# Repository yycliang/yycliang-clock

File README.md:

# yycliang-clock
 My first HPS clock

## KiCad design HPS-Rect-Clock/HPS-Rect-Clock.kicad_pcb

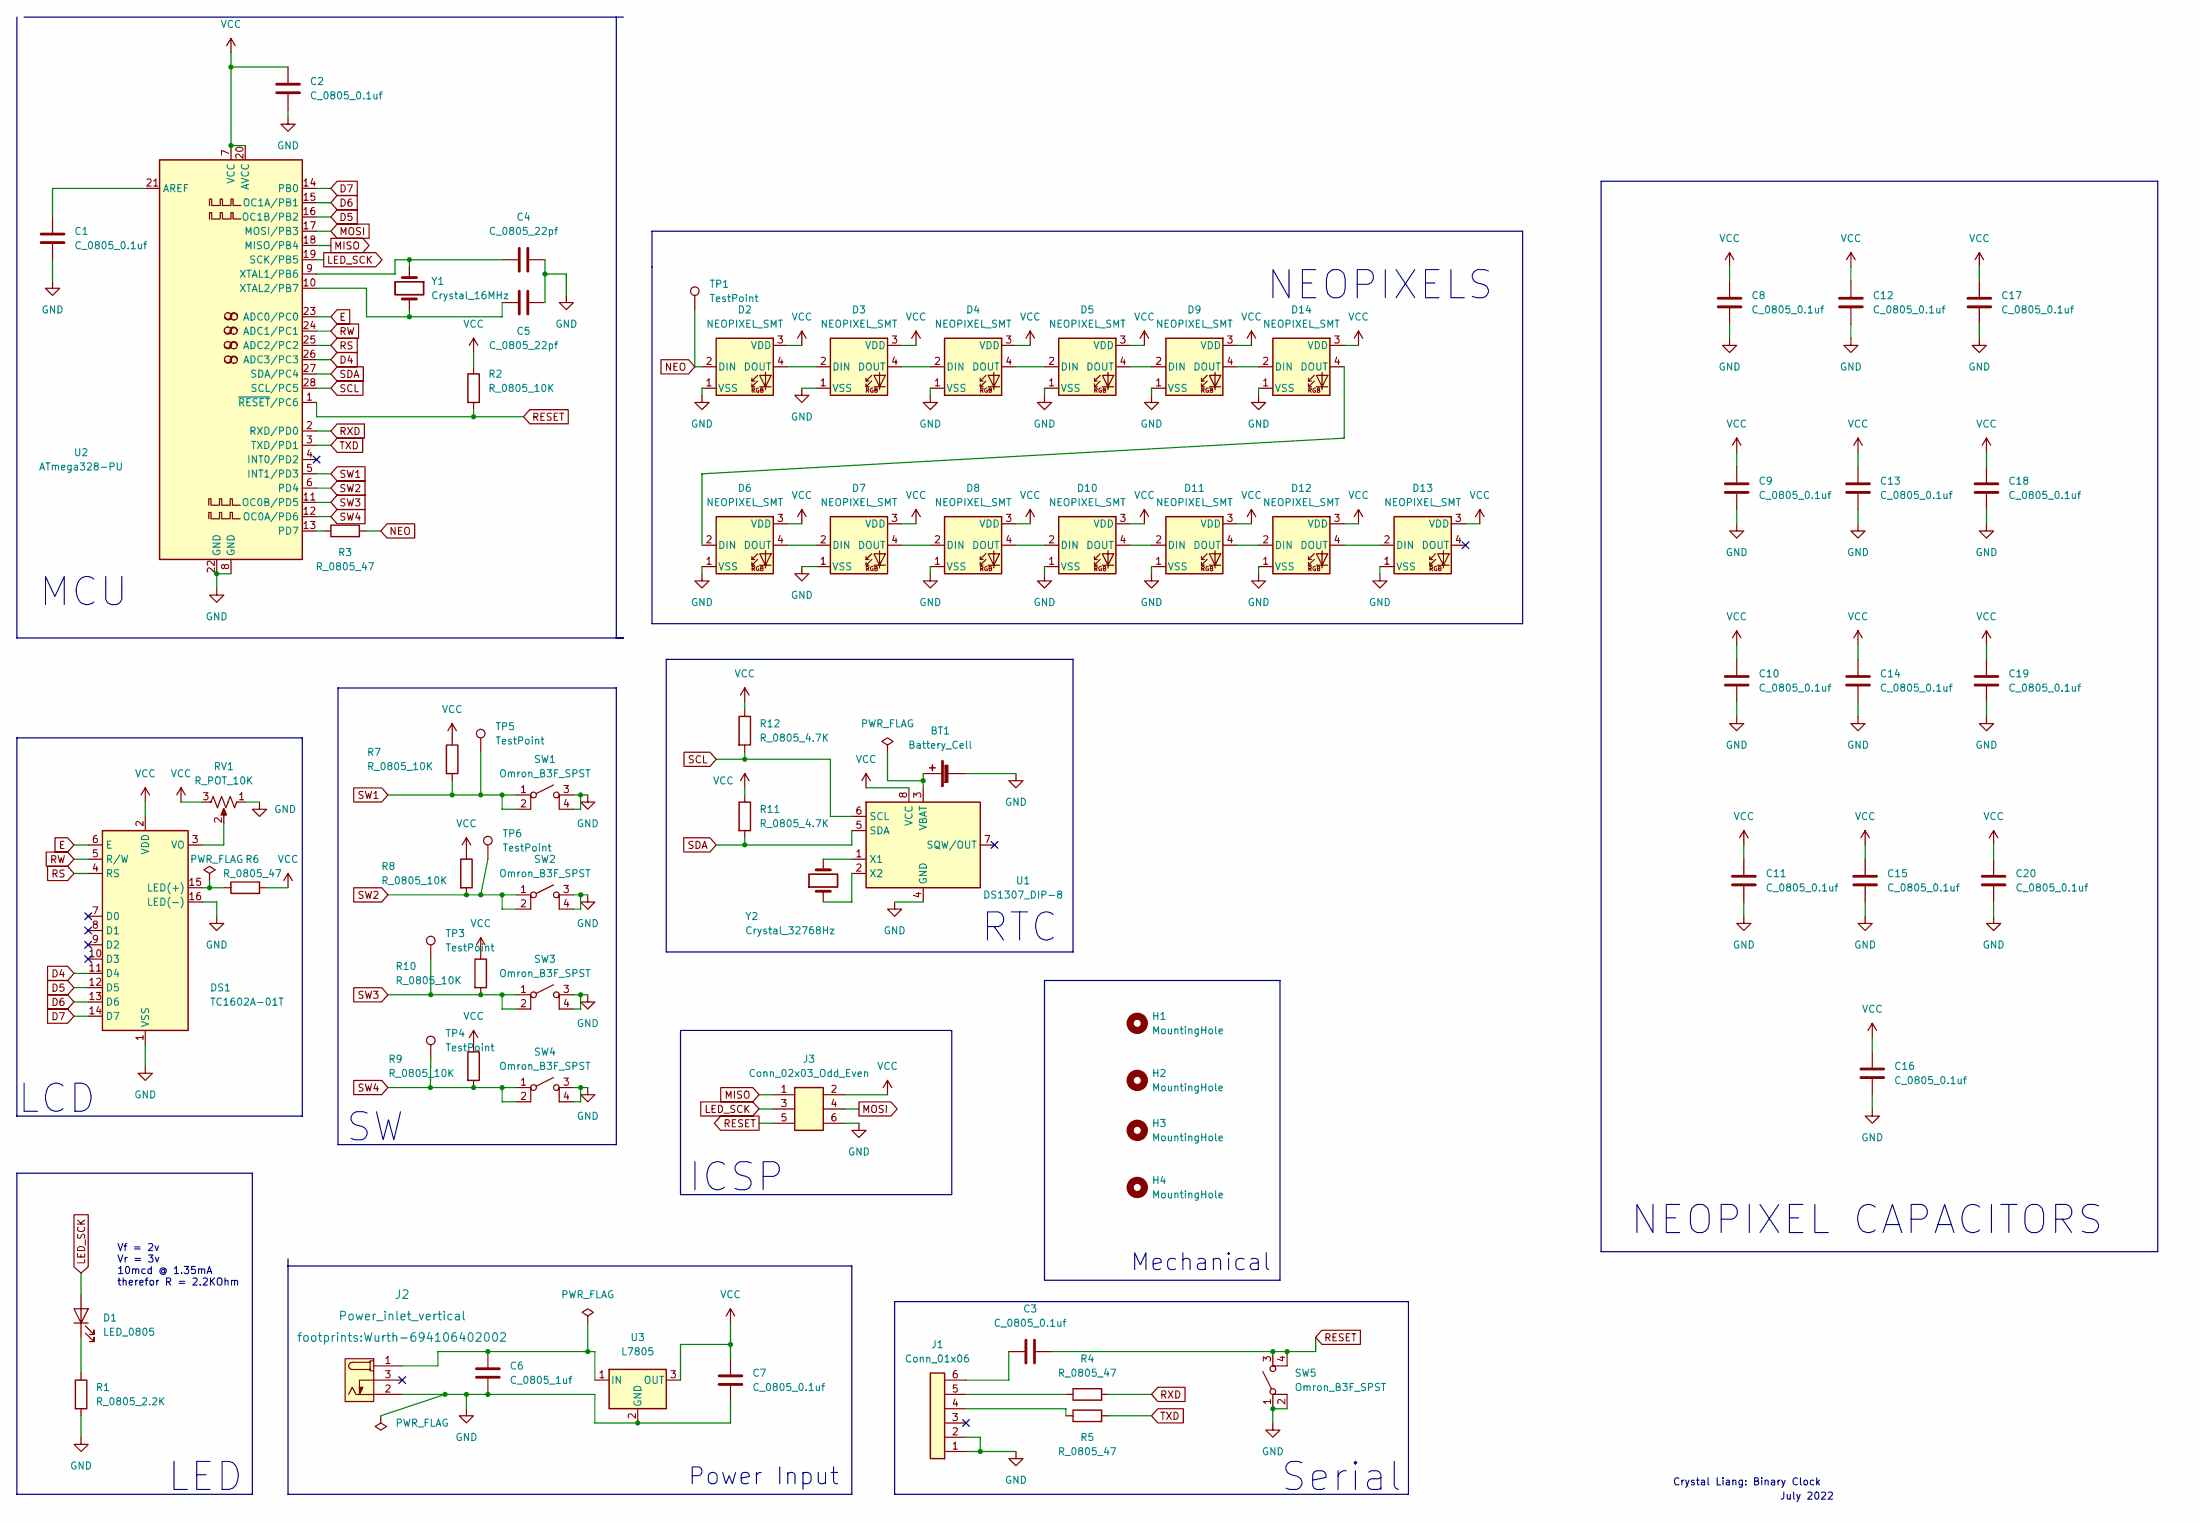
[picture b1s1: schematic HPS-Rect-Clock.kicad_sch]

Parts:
BT1: Battery_Cell; BatteryHolder_Keystone_106_1x20mm; MPN BS-7; Digikey PN BS-7-ND
C1, C2: C_0805_0.1uf; C_0805_2012Metric; Voltage N/A; Tolerance N/A; MPN GRM21BR61E106KA73L; Digikey PN 490-5523-1-ND
C3, C7, C8, C9, C10, C11, C12, C13, C14, C15, C16, C17, C18, C19, C20: C_0805_0.1uf; C_0805_2012Metric; Voltage N/A; Tolerance N/A; MPN 08055C104KAT2A; Digikey PN 478-1395-1-ND
C4, C5: C_0805_22pf; C_0805_2012Metric; Voltage N/A; Tolerance N/A; MPN GRM21BR61E106KA73L; Digikey PN 490-5523-1-ND
C6: C_0805_1uf; C_0805_2012Metric; Voltage N/A; Tolerance N/A; MPN 08055C104KAT2A; Digikey PN 478-1395-1-ND
D1: LED_0805; LED_0805_2012Metric; MPN 150080RS75000; Digikey PN 732-4984-1-ND
D2, D3, D4, D5, D6, D7, D8, D9, D10, D11, D12, D13, D14: NEOPIXEL_SMT; LED_SK6812_PLCC4_5.0x5.0mm_P3.2mm; MPN IN-PI554FCH; Digikey PN 1830-1106-1-ND
DS1: TC1602A-01T; MPN 1447; Digikey PN 1528-2212-ND
H1, H2, H3, H4: MountingHole; MountingHole_3.2mm_M3
J1: Conn_01x06; PinHeader_1x06_P2.54mm_Vertical; MPN 61300611121; Digikey PN 732-5319-ND
J2: Power_inlet_vertical; Wurth-694106402002; MPN 694106402002; Digikey PN 732-5931-ND
J3: Conn_02x03_Odd_Even; PinHeader_2x03_P2.54mm_Vertical; MPN PRPC003DAAN-RC; Digikey PN S2011EC-03-ND
R1: R_0805_2.2K; R_0805_2012Metric; Tolerance N/A; MPN N/A; Digikey PN 311-2.20KCRCT-ND
R2, R7, R8, R9, R10: R_0805_10K; R_0805_2012Metric; Tolerance N/A; MPN RC0805FR-0710KL; Digikey PN 311-10.0KCRCT-ND
R3, R6: R_0805_47; R_0805_2012Metric; Tolerance N/A; Mouser PN N/A; Digikey PN RC0805FR-0747RL
R4, R5: R_0805_47; R_0805_2012Metric; Tolerance N/A; MPN RC0805FR-074K7L; Digikey PN 311-4.70KCRCT-ND
R11, R12: R_0805_4.7K; R_0805_2012Metric; Tolerance N/A; MPN RC0805FR-074K7L; Digikey PN 311-4.70KCRCT-ND
RV1: R_POT_10K; Potentiometer_Bourns_3386P_Vertical; MPN 3386P-1-103TLF; Digikey PN 3386P-103TLF-ND
SW1, SW2, SW3, SW4, SW5: Omron_B3F_SPST; SW_SPST_Omron_B3FS-100xP; MPN B3FS-1000P; Digikey PN SW423CT-ND
TP1, TP3, TP4, TP5, TP6: TestPoint; TestPoint_THTPad_D2.0mm_Drill1.0mm
U1: DS1307_DIP-8; DIP-8_W7.62mm; MPN A 08-LC-TT; Digikey PN AE9986-ND
U2: ATmega328-PU; DIP-28_W7.62mm; MPN ED281DT; Digikey PN ED3050-5-ND
U3: L7805; TO-252-2; MPN L7805CDT-TR; Digikey PN 497-7255-1-ND
Y1: Crystal_16MHz; Crystal_SMD_HC49-SD; MPN ECS-160-20-5PXDN-TR; Digikey PN XC1299CT-ND
Y2: Crystal_32768Hz; Crystal_SMD_2Pin_3.2x1.5mm; MPN Q 0,032768-JTX310-12,5-20-T1-HMR-50K-LF; Digikey PN 1908-1314-1-ND

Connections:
D4: DS1.11 (D4), U2.26 (ADC3/PC3)
D5: DS1.12 (D5), U2.16 (OC1B/PB2)
D6: DS1.13 (D6), U2.15 (OC1A/PB1)
D7: DS1.14 (D7), U2.14 (PB0)
E: DS1.6 (E), U2.23 (ADC0/PC0)
GND: BT1.2 (-), C1.2, C2.2, C4.2, C5.2, C6.1, C7.1, C8.1, C9.1, C10.1, C11.1, C12.1, C13.1, C14.1, C15.1, C16.1, C17.1, C18.1, C19.1, C20.1, D2.1 (VSS), D3.1 (VSS), D4.1 (VSS), D5.1 (VSS), D6.1 (VSS), D7.1 (VSS), D8.1 (VSS), D9.1 (VSS), D10.1 (VSS), D11.1 (VSS), D12.1 (VSS), D13.1 (VSS), D14.1 (VSS), DS1.1 (VSS), DS1.16 (LED(-)), J1.1, J1.2, J2.2 (OUT), J3.6, R1.2, RV1.1, SW1.3 (B), SW1.4 (B), SW2.3 (B), SW2.4 (B), SW3.3 (B), SW3.4 (B), SW4.3 (B), SW4.4 (B), SW5.1 (A), SW5.2 (A), U1.4 (GND), U2.8 (GND), U2.22 (GND), U3.2 (GND)
LED_SCK: D1.2 (A), J3.3, U2.19 (SCK/PB5)
MISO: J3.1, U2.18 (MISO/PB4)
MOSI: J3.4, U2.17 (MOSI/PB3)
NEO: D2.2 (DIN), R3.2, TP1.1
unnamed: BT1.1 (+), U1.3 (VBAT)
unnamed: C1.1, U2.21 (AREF)
unnamed: C3.2, J1.6
unnamed: C4.1, U2.9 (XTAL1/PB6), Y1.1
unnamed: C5.1, U2.10 (XTAL2/PB7), Y1.2
unnamed: C6.2, J2.1 (POLE), U3.1 (IN)
unnamed: D1.1 (K), R1.1
unnamed: D2.4 (DOUT), D3.2 (DIN)
unnamed: D3.4 (DOUT), D4.2 (DIN)
unnamed: D4.4 (DOUT), D5.2 (DIN)
unnamed: D5.4 (DOUT), D9.2 (DIN)
unnamed: D6.4 (DOUT), D7.2 (DIN)
unnamed: D7.4 (DOUT), D8.2 (DIN)
unnamed: D8.4 (DOUT), D10.2 (DIN)
unnamed: D10.4 (DOUT), D11.2 (DIN)
unnamed: D11.4 (DOUT), D12.2 (DIN)
unnamed: D12.4 (DOUT), D13.2 (DIN)
unnamed: D9.4 (DOUT), D14.2 (DIN)
unnamed: D6.2 (DIN), D14.4 (DOUT)
unnamed: DS1.3 (VO), RV1.2
unnamed: DS1.15 (LED(+)), R6.1
unnamed: J1.4, R5.1
unnamed: J1.5, R4.1
unnamed: R3.1, U2.13 (PD7)
unnamed: U1.1 (X1), Y2.2
unnamed: U1.2 (X2), Y2.1
RESET: C3.1, J3.5, R2.2, SW5.3 (B), SW5.4 (B), U2.1 (~RESET/PC6)
RS: DS1.4 (RS), U2.25 (ADC2/PC2)
RW: DS1.5 (R/W), U2.24 (ADC1/PC1)
RXD: R4.2, U2.2 (RXD/PD0)
SCL: R12.2, U1.6 (SCL), U2.28 (SCL/PC5)
SDA: R11.2, U1.5 (SDA), U2.27 (SDA/PC4)
SW1: R7.2, SW1.1 (A), SW1.2 (A), TP5.1, U2.5 (INT1/PD3)
SW2: R8.2, SW2.1 (A), SW2.2 (A), TP6.1, U2.6 (PD4)
SW3: R10.2, SW3.1 (A), SW3.2 (A), TP3.1, U2.11 (OC0B/PD5)
SW4: R9.2, SW4.1 (A), SW4.2 (A), TP4.1, U2.12 (OC0A/PD6)
TXD: R5.2, U2.3 (TXD/PD1)
VCC: C2.1, C7.2, C8.2, C9.2, C10.2, C11.2, C12.2, C13.2, C14.2, C15.2, C16.2, C17.2, C18.2, C19.2, C20.2, D2.3 (VDD), D3.3 (VDD), D4.3 (VDD), D5.3 (VDD), D6.3 (VDD), D7.3 (VDD), D8.3 (VDD), D9.3 (VDD), D10.3 (VDD), D11.3 (VDD), D12.3 (VDD), D13.3 (VDD), D14.3 (VDD), DS1.2 (VDD), J3.2, R2.1, R6.2, R7.1, R8.1, R9.1, R10.1, R11.1, R12.1, RV1.3, U1.8 (VCC), U2.7 (VCC), U2.20 (AVCC), U3.3 (OUT)

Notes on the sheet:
July 2022
MCU
ICSP
RTC
Serial
LCD
NEOPIXEL CAPACITORS
NEOPIXELS
LED
Mechanical
Crystal Liang: Binary Clock
Power Input
Vf = 2v Vr = 3v 10mcd @ 1.35mA therefor R = 2.2KOhm

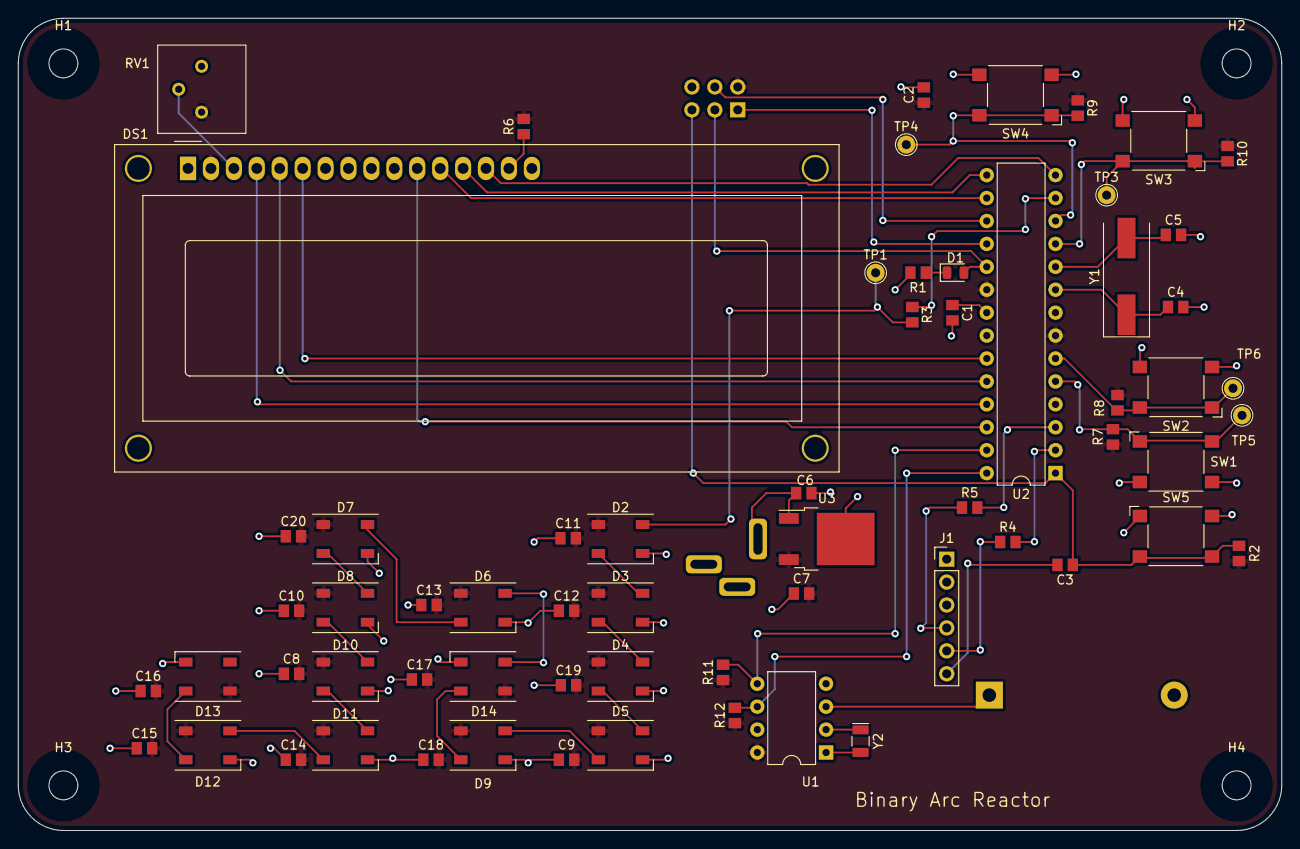
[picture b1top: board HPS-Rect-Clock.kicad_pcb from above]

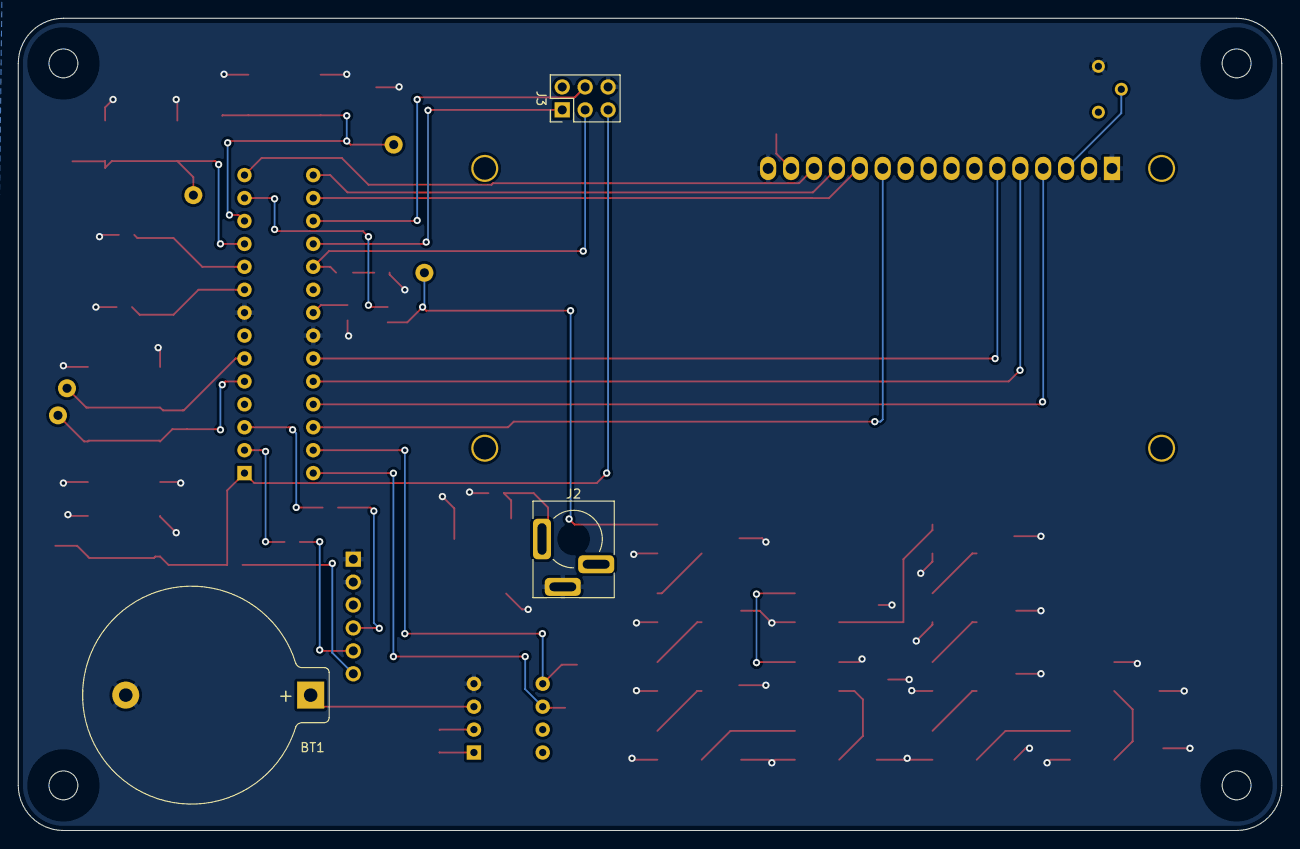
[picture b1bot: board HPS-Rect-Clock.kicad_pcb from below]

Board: 2 copper layers, 140.0 x 90.0 mm, 71 parts (3 on the bottom side), 48 nets.

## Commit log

2022-06-01 Template Documents
2022-06-13 Week 1 Schematics
2022-06-19 Week 2
2022-06-25 Week 3
2022-07-07 Week 4
2022-07-08 Week 5
2022-07-08 LCD Edits
2022-07-17 Week 6: Pre route
2022-07-18 PCB Placement Done
2022-07-18 PCB routing done p2
2022-07-18 Starting Traces
2022-07-18 Moderate amount of tracing done
2022-07-18 Tracing nearly done
2022-07-18 only gnd left
2022-07-18 Routing Complete
2022-07-19 GND and vertical and horizontal
2022-07-19 test points added
2022-07-21 Pre Gerber Edits
2022-07-21 PreGerber Edits
2022-07-21 Pre Gerber Edits - DRC
2022-07-21 Updated Library and SDA and SCL pin
2022-07-22 Schematic Changes for Wiring
2022-07-22 Gerber out all done
2022-07-23 Gerber Out 2.0
2022-08-24 Binary Clock
